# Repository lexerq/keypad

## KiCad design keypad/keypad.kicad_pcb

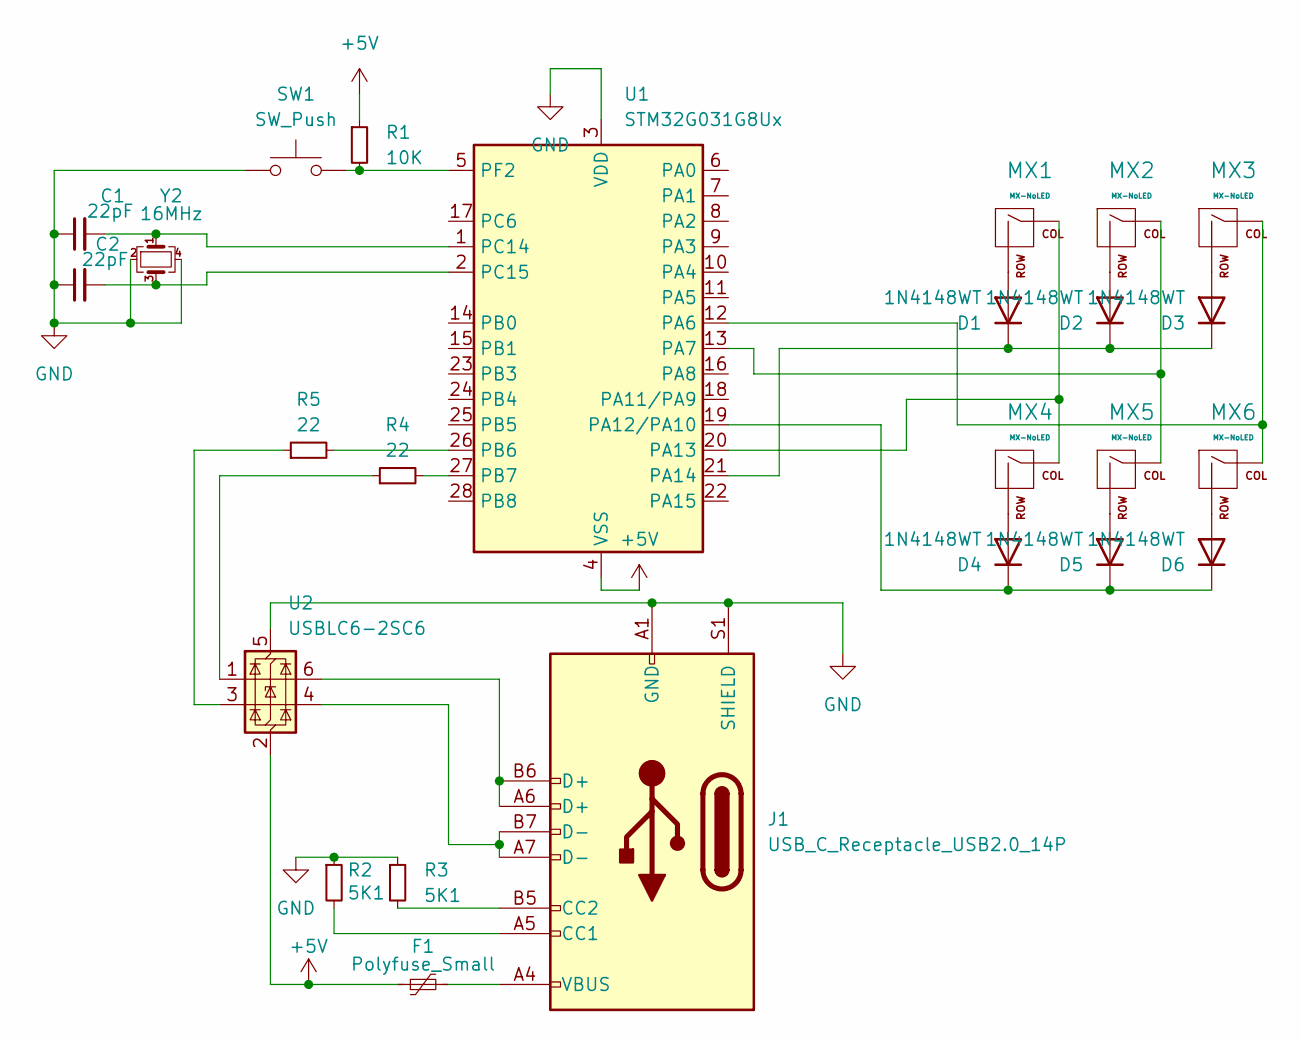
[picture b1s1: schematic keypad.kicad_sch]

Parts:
C1, C2: 22pF; C_0805_2012Metric
D1, D2, D3, D4, D5, D6: 1N4148WT; D_SOD-523
F1: Polyfuse_Small; PF0805
J1: USB_C_Receptacle_USB2.0_14P; USB_C_Receptacle_GCT_USB4105-xx-A_16P_TopMnt_Horizontal
MX1, MX2, MX3, MX4, MX5, MX6: MX-NoLED; SW_Cherry_MX_1.00u_PCB
R1: 10K; R_0805_2012Metric
R2, R3: 5K1; R_0805_2012Metric
R4, R5: 22; R_0805_2012Metric
SW1: SW_Push; SW_Push_1P1T_NO_6x6mm_H9.5mm
U1: STM32G031G8Ux; QFN-28_4x4mm_P0.5mm
U2: USBLC6-2SC6; SOT-23-6
Y2: 16MHz; Crystal_SMD_3225-4Pin_3.2x2.5mm

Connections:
+5V: F1.1, R1.1, U1.4 (VSS), U2.2 (GND)
GND: C1.1, C2.1, J1.A1 (GND), J1.A12 (GND), J1.B1 (GND), J1.B12 (GND), J1.S1 (SHIELD), R2.1, R3.1, SW1.1, U1.3 (VDD), U2.5 (VBUS), Y2.2, Y2.4
unnamed: D1.2 (A), MX1.2 (ROW)
unnamed: D1.1 (K), D2.1 (K), D3.1 (K), U1.21 (PA14)
unnamed: D2.2 (A), MX2.2 (ROW)
unnamed: D3.2 (A), MX3.2 (ROW)
unnamed: D4.2 (A), MX4.2 (ROW)
unnamed: D4.1 (K), D5.1 (K), D6.1 (K), U1.19 (PA12/PA10)
unnamed: D5.2 (A), MX5.2 (ROW)
unnamed: D6.2 (A), MX6.2 (ROW)
unnamed: F1.2, J1.A4 (VBUS), J1.A9 (VBUS), J1.B4 (VBUS), J1.B9 (VBUS)
unnamed: J1.A5 (CC1), R2.2
unnamed: J1.B5 (CC2), R3.2
unnamed: J1.A6 (D+), J1.B6 (D+), U2.6 (I/O1)
unnamed: J1.A7 (D-), J1.B7 (D-), U2.4 (I/O2)
unnamed: MX1.1 (COL), MX4.1 (COL), U1.20 (PA13)
unnamed: MX2.1 (COL), MX5.1 (COL), U1.13 (PA7)
unnamed: MX3.1 (COL), MX6.1 (COL), U1.12 (PA6)
unnamed: R4.1, U2.1 (I/O1)
unnamed: R5.1, U2.3 (I/O2)
unnamed: R5.2, U1.26 (PB6)
unnamed: R4.2, U1.27 (PB7)
unnamed: C1.2, U1.1 (PC14), Y2.1
unnamed: C2.2, U1.2 (PC15), Y2.3
unnamed: R1.2, SW1.2, U1.5 (PF2)

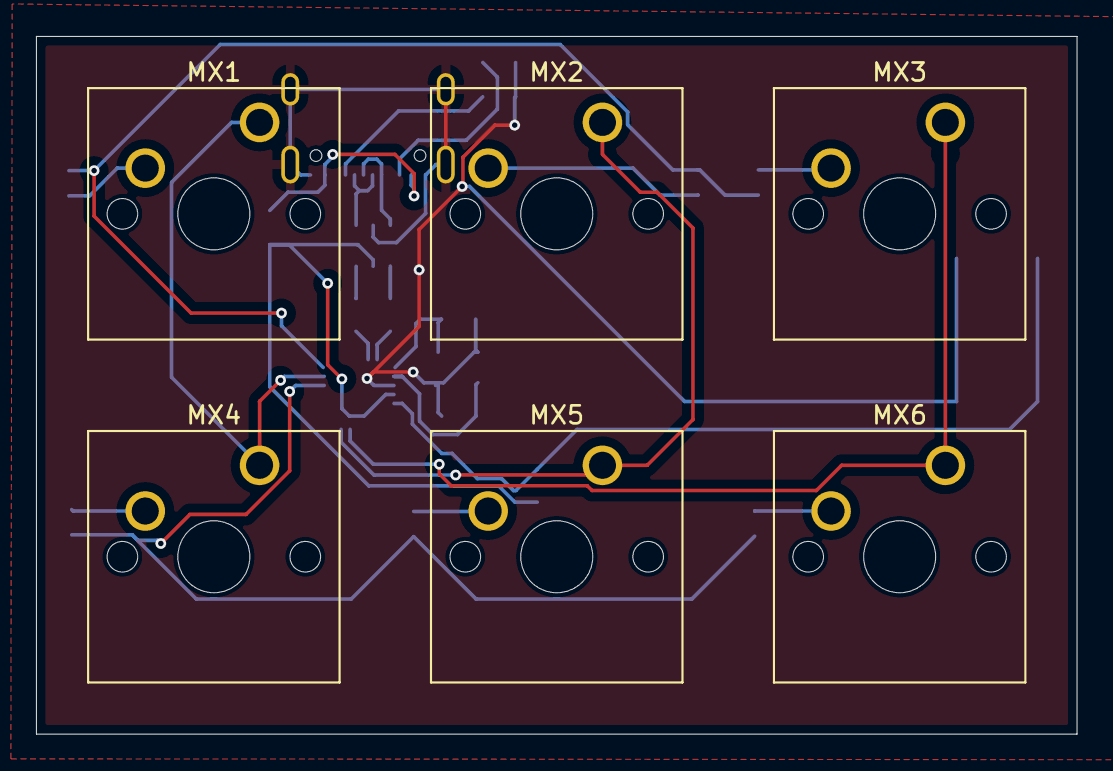
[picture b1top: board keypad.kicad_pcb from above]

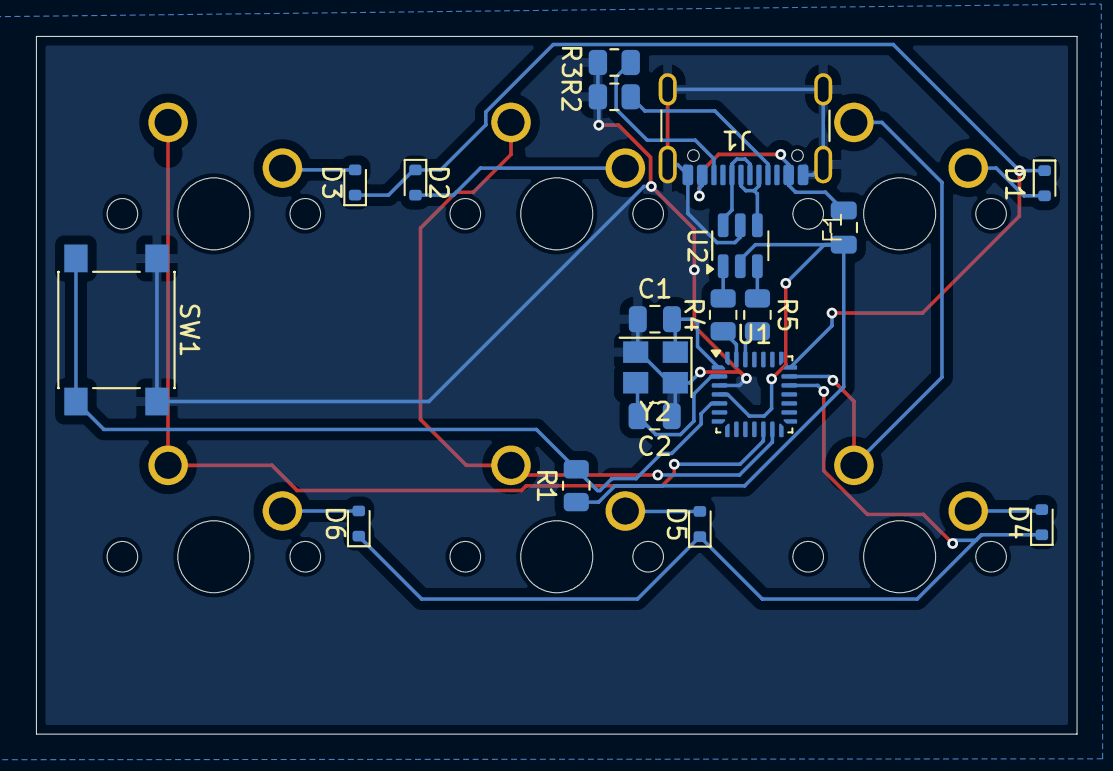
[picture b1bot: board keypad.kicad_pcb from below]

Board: 2 copper layers, 57.8 x 38.8 mm, 25 parts (19 on the bottom side), 25 nets.

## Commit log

2024-12-22 main
